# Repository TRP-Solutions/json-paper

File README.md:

# JSON Paper

See the [GitHub wiki](https://github.com/TRP-Solutions/json-paper/wiki) for project documentation.

## Hardware

| Brand | Model |
|---|---|
| Espressif | ESP32-C5-DevKitC-1 v1.2 with 8 MB PSRAM |
| Waveshare | 5.79inch e-Paper Module (G), SKU 27846 |

## Wiring

| E-paper connection | ESP32-C5 connection |
|---|--------------------:|
| PWR |               GPIO5 |
| BUSY |              GPIO9 |
| RST |              GPIO8 |
| DC |               GPIO4 |
| CS |              GPIO10 |
| CLK |               GPIO6 |
| DIN |               GPIO7 |
| GND |                 GND |
| VCC (Pin 1) |                  5V |

| Accessory connection | ESP32-C5 connection |
|----------------------|--------------------:|
| Setup button         |               GPIO0 |
| Setup button GND     |                 GND |

## Pie charts

Use one `draw_pie_slice` command for each colored section. Every slice accepts:

| Argument | Meaning |
|---|---|
| `x`, `y` | Center of the chart |
| `radius` | Slice radius in pixels |
| `start_angle` | Starting angle in degrees |
| `sweep_angle` | Clockwise size from 1° through 360° |
| `color` | `white`, `black`, `red`, or `yellow` |

Zero degrees points right. Angles increase clockwise: 90° points down, 180°
points left, and 270° points up. Starting angles outside 0–359° are normalized.
Later commands paint over earlier commands when slices overlap.

This example draws a radius-80 chart containing 25% red, 35% yellow, and 40%
black:

```json
{
  "version": "1.0",
  "commands": [
    {
      "cmd": "draw_pie_slice",
      "args": {
        "x": 200,
        "y": 135,
        "radius": 80,
        "start_angle": 270,
        "sweep_angle": 90,
        "color": "red"
      }
    },
    {
      "cmd": "draw_pie_slice",
      "args": {
        "x": 200,
        "y": 135,
        "radius": 80,
        "start_angle": 0,
        "sweep_angle": 126,
        "color": "yellow"
      }
    },
    {
      "cmd": "draw_pie_slice",
      "args": {
        "x": 200,
        "y": 135,
        "radius": 80,
        "start_angle": 126,
        "sweep_angle": 144,
        "color": "black"
      }
    }
  ]
}
```

The PHP helper provides the equivalent method:

```php
$display
    ->pieSlice(200, 135, 80, 270, 90, Color::RED)
    ->pieSlice(200, 135, 80, 0, 126, Color::YELLOW)
    ->pieSlice(200, 135, 80, 126, 144, Color::BLACK);
```

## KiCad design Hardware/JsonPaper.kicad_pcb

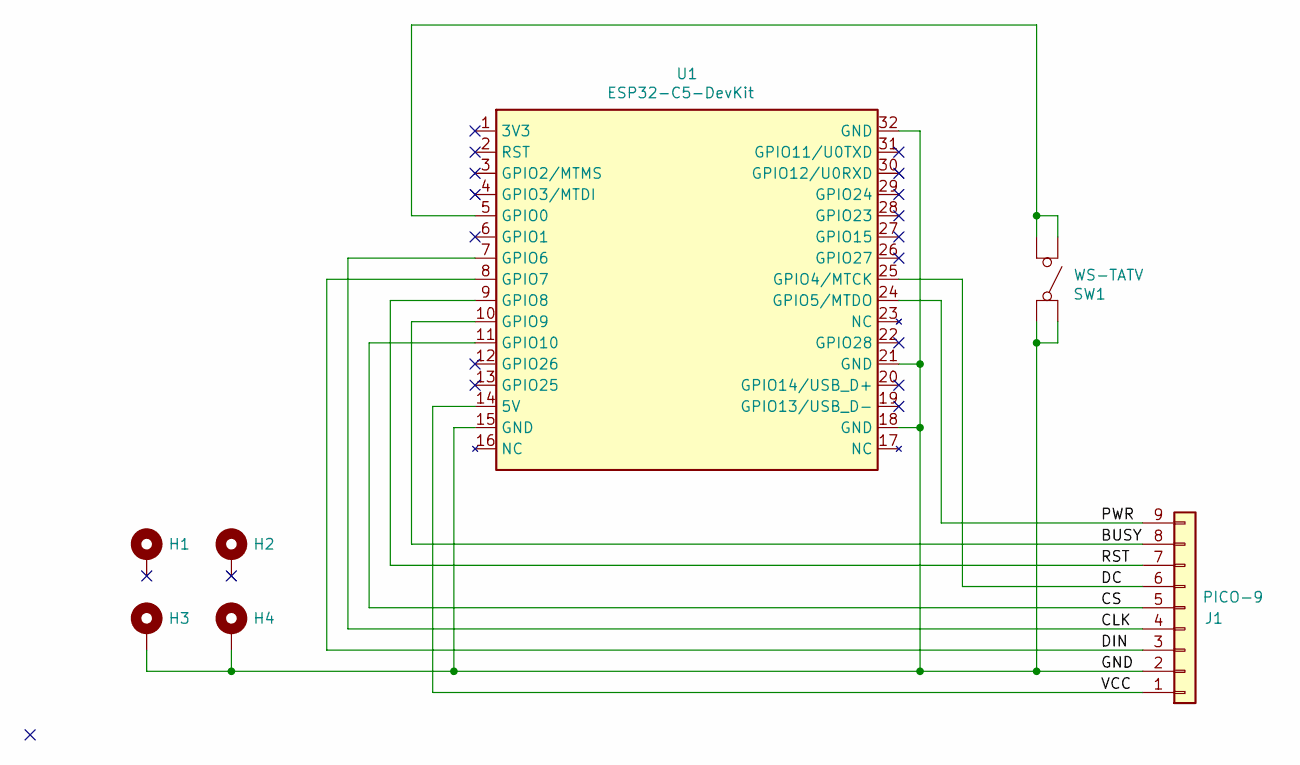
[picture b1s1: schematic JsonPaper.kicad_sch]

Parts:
H1, H2, H3, H4: MountingHole_Pad; MountingHole_2.7mm_M2.5_Pad_Via
J1: PICO-9; Molex_PicoBlade_1x09_P1.25mm_Horizontal; Part number 53048-0910
SW1: WS-TATV; SW_PUSH_6mm; Part number 430156043726
U1: ESP32-C5-DevKit; ESP32-C5-DevKitC-1; Part number ESP32-C5-DevKitC-1-N8R8

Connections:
/BUSY: J1.8, U1.10 (GPIO9)
/CLK: J1.4, U1.7 (GPIO6)
/CS: J1.5, U1.11 (GPIO10)
/DC: J1.6, U1.25 (GPIO4/MTCK)
/DIN: J1.3, U1.8 (GPIO7)
/GND: H3.1 (1_1), H4.1 (1_1), J1.2, SW1.1 (A1), SW1.3 (A2), U1.15 (GND), U1.18 (GND), U1.21 (GND), U1.32 (GND)
/PWR: J1.9, U1.24 (GPIO5/MTDO)
/RST: J1.7, U1.9 (GPIO8)
/VCC: J1.1, U1.14 (5V)
unnamed: SW1.2 (B1), SW1.4 (B2), U1.5 (GPIO0)

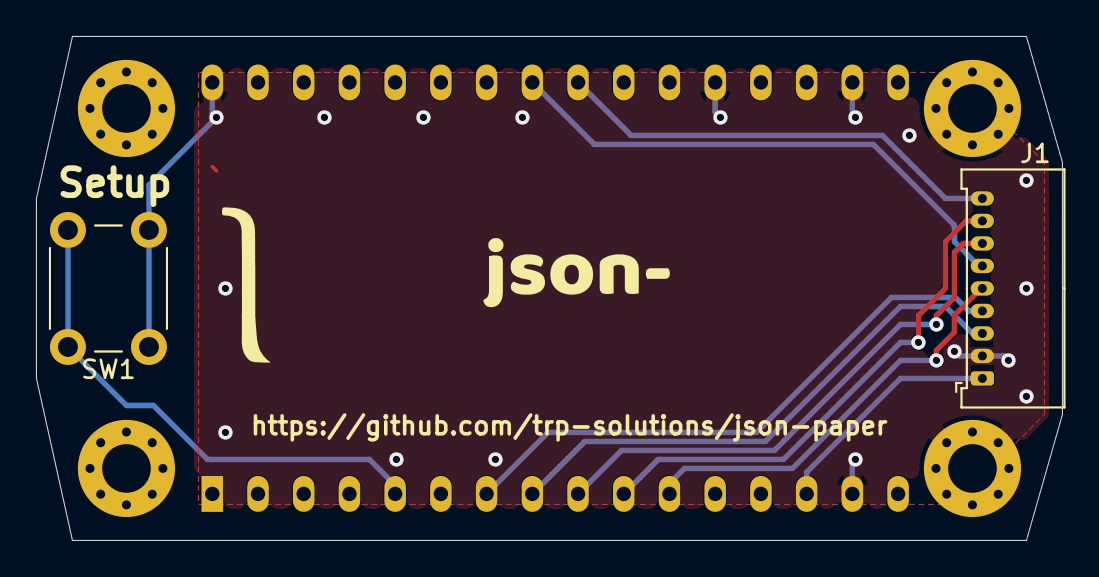
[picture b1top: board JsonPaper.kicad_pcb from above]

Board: 2 copper layers, 57.0 x 28.0 mm, 7 parts (0 on the bottom side), 10 nets.

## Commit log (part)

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2026-04-01 Folder structure
2026-04-01 refractor whole project file structure
2026-04-01 removed sample images and refrecated file names
2026-04-01 made github workflow install latest version of cmake
2026-04-01 refactored command structure and updated GitHub workflow dependencies
2026-04-01 update GitHub workflow to ensure CMake is installed before configuration steps
2026-04-01 refactored file names to use consistent lowercase naming and updated related references
2026-04-01 standardize header file naming to lowercase in Emulator/CMakeLists.txt
2026-04-01 standardize header file naming to lowercase in gui_raylib.cpp
2026-04-01 update GitHub workflow to package artifacts and create releases for tagged versions
2026-04-01 conditionally skip builds for tagged refs and compress macOS artifact as a zip file
2026-04-01 split build and release workflows; simplify build configuration and add automated release creation
2026-04-01 remove redundant newline in debug.h
2026-04-01 remove redundant newline in button.h
2026-04-01 add tests for macOS, Windows, and Linux builds in GitHub workflow
2026-04-01 improve macOS app test workflow: ensure proper process handling and delay handling
2026-04-27 standardize naming of `command` to `PaperCommand` and update header inclusions accordingly; implement `ConsoleManager` with a registry for console commands
2026-04-27 embed font data into emulator, remove assets path dependency in debug builds
2026-04-27 update `log` method to use `const char*` instead of `std::string` for format strings, ensuring compatibility with `vsnprintf` and standardizing logging calls
2026-04-27 replace C-style casts with uniform initialization for `Color` objects in console drawing functions
2026-04-27 add `WIN32` flag to Windows build target in CMakeLists to fix window subsystem linking
2026-04-27 add `/SUBSYSTEM:WINDOWS` linker option for Windows build target in CMakeLists to ensure proper subsystem configuration
2026-04-27 add `/ENTRY:mainCRTStartup` linker option for Windows build target to specify entry point in CMakeLists
2026-04-29 add text selection, clipboard operations (Ctrl+C, Ctrl+V), and selection-aware cursor behavior in console
2026-05-05 added image support and support for drawing strings without a background
2026-05-06 added readme file and sample file
2026-05-06 removed readme as we now use github wiki
2026-05-07 safer rendering with more warnings coming in console
2026-05-07 Created Display class for easier JSON manipulation with test samples
2026-05-08 made e-paper own most of logic and used #ifdef to see what we are compiling to
2026-05-08 Add ino-file to connect arduino to wifi & get json from url
2026-05-08 add arduino header-file
2026-05-08 updated CMakeLists.txt with new file names
2026-05-08 Added logo
2026-05-08 started with splitting core.cpp apart into smaller files
2026-05-08 removed constexpr
2026-05-08 Update logo used in sample
2026-05-08 moved function out of core into separate files
2026-05-08 changed std::string lastExecutedText = ""; to std::string lastExecutedText;
2026-05-08 main cleanup
2026-05-08 Add error handling to request- & parse function
2026-05-08 include algorithim before deque
2026-05-08 Remove unwanted data
2026-05-11 Add Datasheets
2026-05-11 remapped debug/debug.h to debug_custom/debug.h
2026-05-11 core.h now include debug_custom/debug.h instead of debug/debug.h instead
2026-05-11 Remove VSCode extensions file
2026-05-11 removed GDImage from php library and updated so coordinates now is 0 indexed
2026-05-11 mde all Arduino files include path relative
2026-05-11 Arduino includes is now only included for Arduino builds
2026-05-11 added debug to epd header
2026-05-11 Edit functions in "request.cpp" to fix errorsEdit functions in "request.cpp" to fix errors
2026-05-20 optimised for more flash space
2026-05-20 Fix log for "RequestConfig" function & trying to error-fix 'Initialize e-paper screen to display JSON-input'
2026-05-20 Change so arduino connects to wifi before view content on display & Change EDP-width and EDP-height & Fix 'log' function so i print log-messages
2026-05-21 Initialize e-paper screen to display JSON-input
2026-05-21 Add delay for how often EPD-picture needs to update, but still can be affected by the button
2026-05-26 updated sample to use named parameters
2026-06-03 Remove redundant code & Add styling for AP
2026-06-04 Get json-paper logo & change design & fix error in php sample
2026-06-04 missing linebreak in bottom of header-file

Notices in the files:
Hardware/JsonPaper.kicad_pcb:
Apache License 2.0
